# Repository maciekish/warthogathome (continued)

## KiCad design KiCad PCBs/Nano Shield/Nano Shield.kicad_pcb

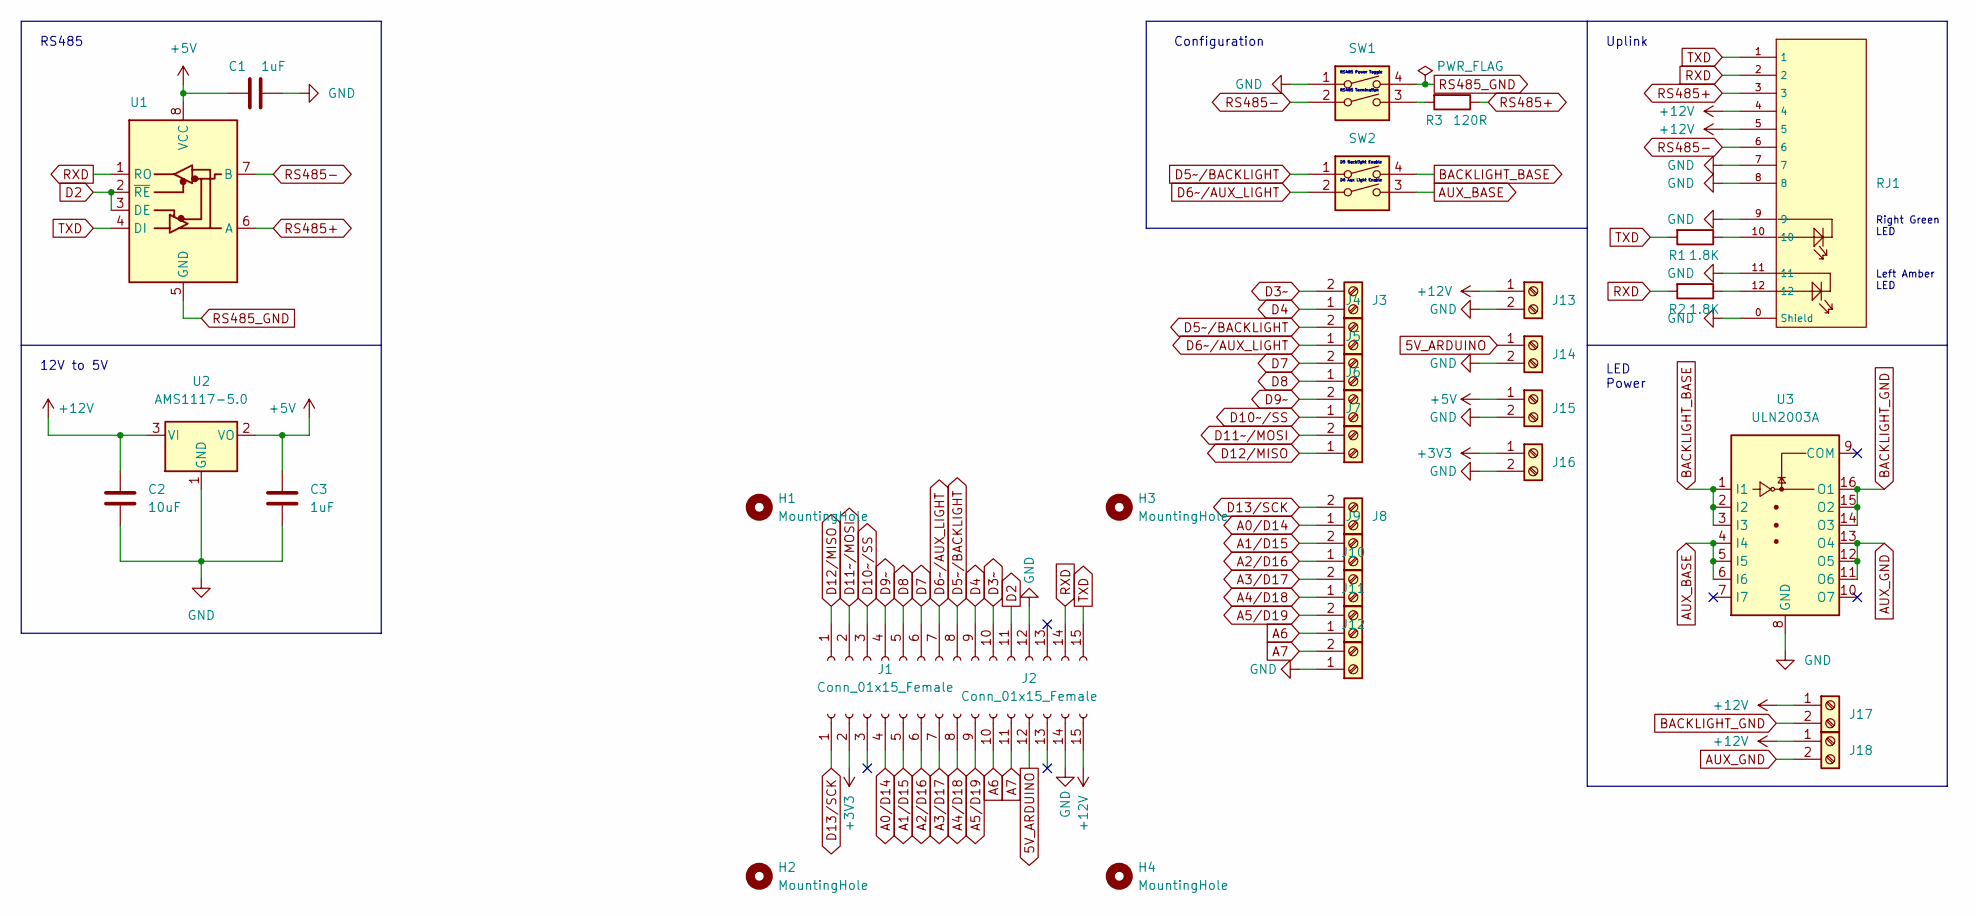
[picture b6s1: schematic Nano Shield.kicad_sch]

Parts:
C1, C3: 1uF; C0402; LCSC C52923
C2: 10uF; C0402; LCSC C15525
H1: MountingHole
H2, H3, H4: MountingHole; MountingHole_3.2mm_M3
J1, J2: Conn_01x15_Female; PinSocket_1x15_P2.54mm_Vertical
J3, J4, J5, J6, J7, J8, J9, J10, J11, J12, J13, J14, J15, J16, J17, J18: Screw_Terminal_01x02; CONN-TH_XY308-2.54-2P; LCSC C557685
R1, R2: 1.8K; R_0805_2012Metric; LCSC C17398
R3: 120R; R_0805_2012Metric; LCSC C17437
RJ1: RJ45-B-1*1; RJ45-TH_B-1-1; LCSC C138392
SW1, SW2: SW_DIP_x02; SW-SMD_DSHP02TSGER; LCSC C367376
U1: MAX487ESA+T; SOIC-8_L5.0-W4.0-P1.27-LS6.0-BL; LCSC C9953
U2: AMS1117-5.0; SOT-223-3_TabPin2; LCSC C6187
U3: ULN2003A; SOP-16_L10.0-W3.9-P1.27-LS6.0-BL; LCSC C7512

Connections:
5V_ARDUINO: J2.12, J14.1
+3V3: J2.2, J16.1
+5V: C1.1, C3.1, J15.1, U1.8 (VCC), U2.2 (VO)
+12V: C2.1, J2.15, J13.1, J17.1, J18.1, RJ1.4, RJ1.5, U2.3 (VI)
A0/D14: J2.4, J8.1
A1/D15: J2.5, J9.2
A2/D16: J2.6, J9.1
A3/D17: J2.7, J10.2
A4/D18: J2.8, J10.1
A5/D19: J2.9, J11.2
A6: J2.10, J11.1
A7: J2.11, J12.2
AUX_BASE: SW2.3, U3.4 (I4), U3.5 (I5), U3.6 (I6)
AUX_GND: J18.2, U3.11 (O6), U3.12 (O5), U3.13 (O4)
BACKLIGHT_BASE: SW2.4, U3.1 (I1), U3.2 (I2), U3.3 (I3)
BACKLIGHT_GND: J17.2, U3.14 (O3), U3.15 (O2), U3.16 (O1)
D2: J1.11, U1.2 (~RE), U1.3 (DE)
D3~: J1.10, J3.2
D4: J1.9, J3.1
D5~/BACKLIGHT: J1.8, J4.2, SW2.1
D6~/AUX_LIGHT: J1.7, J4.1, SW2.2
D7: J1.6, J5.2
D8: J1.5, J5.1
D9~: J1.4, J6.2
D10~/SS: J1.3, J6.1
D11~/MOSI: J1.2, J7.2
D12/MISO: J1.1, J7.1
D13/SCK: J2.1, J8.2
GND: C1.2, C2.2, C3.2, J1.12, J2.14, J12.1, J13.2, J14.2, J15.2, J16.2, RJ1.0 (Shield), RJ1.7, RJ1.8, RJ1.9, RJ1.11, SW1.1, U2.1 (GND), U3.8 (GND)
unnamed: R1.1, RJ1.10
unnamed: R2.1, RJ1.12
unnamed: R3.2, SW1.3
RS485+: R3.1, RJ1.3, U1.6 (A)
RS485-: RJ1.6, SW1.2, U1.7 (B)
RS485_GND: SW1.4, U1.5 (GND)
RXD: J1.14, R2.2, RJ1.2, U1.1 (RO)
TXD: J1.15, R1.2, RJ1.1, U1.4 (DI)

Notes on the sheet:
D5 Backlight Enable
LED Power
Right Green LED
RS485 Power Toggle
Uplink
12V to 5V
D6 Aux Light Enable
Left Amber LED
RS485 Termination
Configuration
RS485

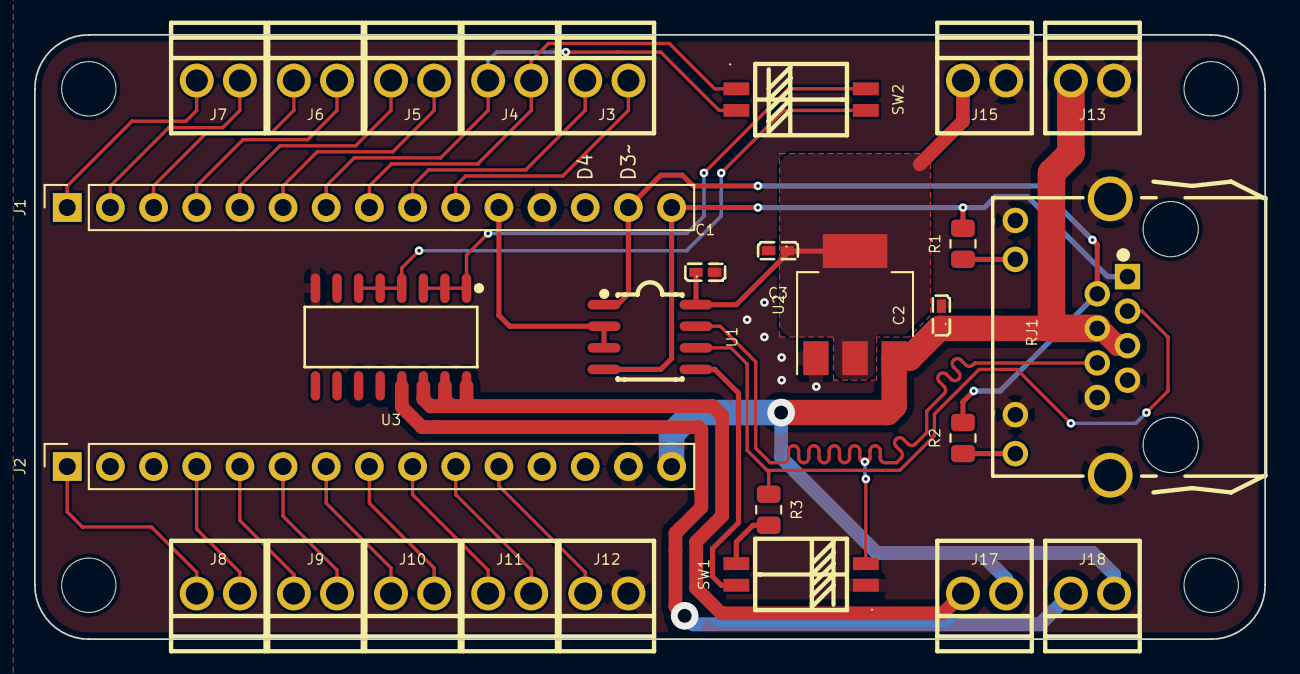
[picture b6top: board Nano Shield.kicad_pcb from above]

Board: 2 copper layers, 72.4 x 35.6 mm, 32 parts (0 on the bottom side), 35 nets.

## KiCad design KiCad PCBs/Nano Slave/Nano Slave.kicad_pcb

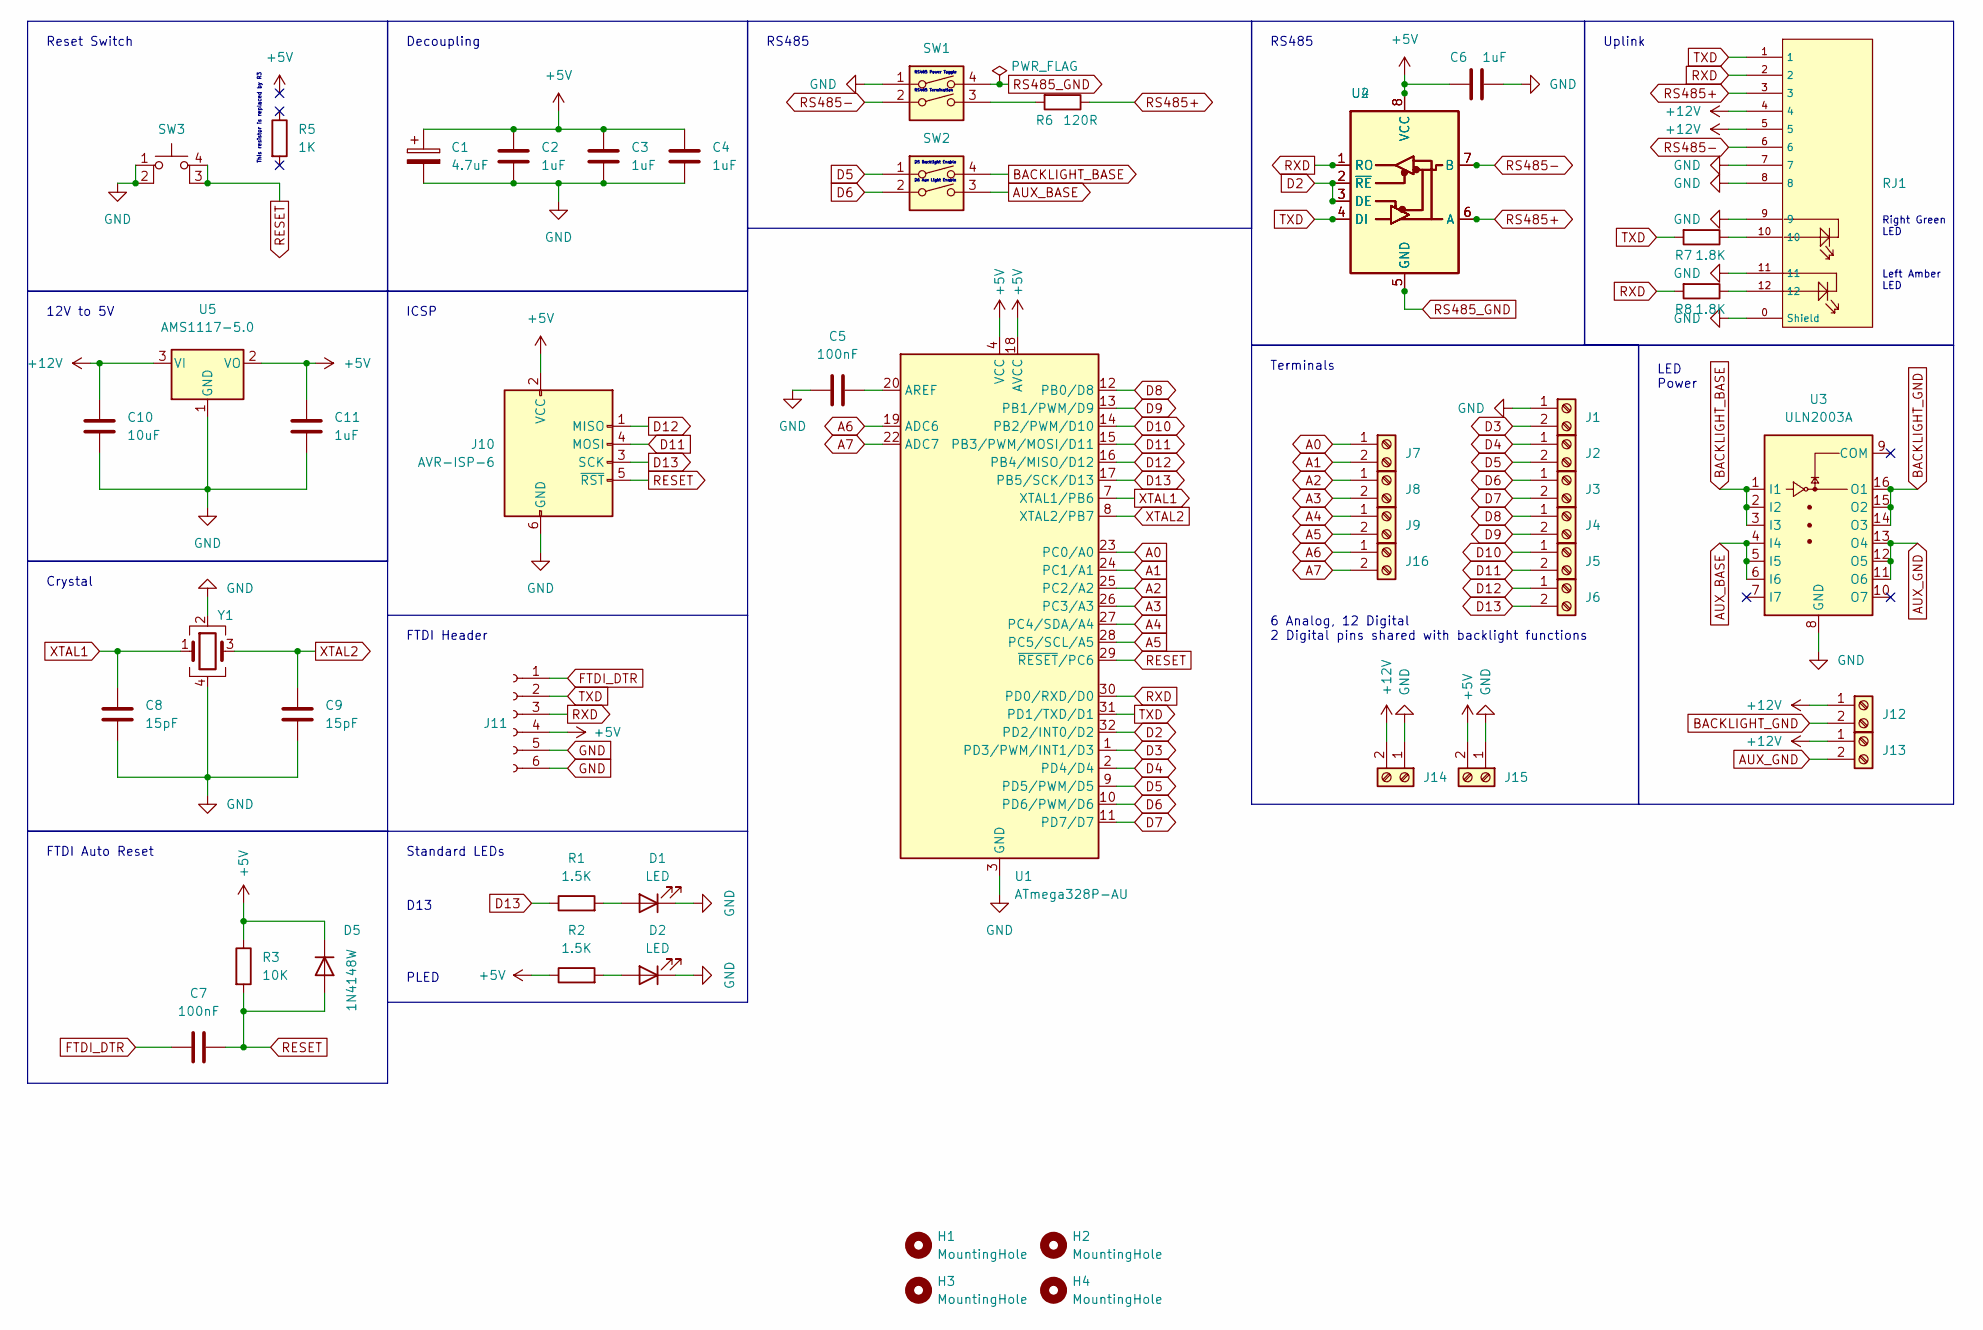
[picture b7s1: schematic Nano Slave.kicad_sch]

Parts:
C1: 4.7uF; C0805; LCSC C1779
C2, C3, C4, C6, C11: 1uF; C0402; LCSC C52923
C5, C7: 100nF; C0402; LCSC C1525
C8, C9: 15pF; C0402; LCSC C1548
C10: 10uF; C0402; LCSC C15525
D1, D2: LED; LED_0603_1608Metric; LCSC C72041
D5: 1N4148W; D_SOD-123; LCSC C81598
H1, H2, H3, H4: MountingHole; MountingHole_3.2mm_M3
J1, J2, J3, J4, J5, J6, J7, J8, J9, J12, J13, J14, J15, J16: Screw_Terminal_01x02; CONN-TH_WJ126V-5.0-2P; LCSC C8404
J10: AVR-ISP-6; PinHeader_2x03_P2.54mm_Vertical; LCSC C492420
J11: Conn_01x06_Female; PinSocket_1x06_P2.54mm_Vertical; LCSC C40877
R1, R2: 1.5K; R_0805_2012Metric; LCSC C4310
R3: 10K; R_0805_2012Metric; LCSC C17414
R5: 1K; R_0805_2012Metric; LCSC C17513
R6: 120R; R_0805_2012Metric; LCSC C17437
R7, R8: 1.8K; R_0805_2012Metric; LCSC C17398
RJ1: RJ45-B-1*1; RJ45-TH_B-1-1; LCSC C138392
SW1, SW2: SW_DIP_x02; SW-SMD_DSHP02TSGER; LCSC C367376
SW3: SW_MEC_5E; SW-SMD_4P-L5.1-W5.1-P3.70-LS6.5-TL-2; LCSC C318884
U1: ATmega328P-AU; TQFP-32_7x7mm_P0.8mm; LCSC C14877
U2: MAX487ESA+T; SOIC-8_L5.0-W4.0-P1.27-LS6.0-BL; LCSC C9953
U3: ULN2003A; SOP-16_L10.0-W3.9-P1.27-LS6.0-BL; LCSC C7512
U4: MAX487CPA+; DIP-8_W7.62mm
U5: AMS1117-5.0; SOT-223-3_TabPin2; LCSC C6187
Y1: Crystal_GND24; Crystal_SMD_3225-4Pin_3.2x2.5mm; LCSC C13738

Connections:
+5V: C1.1, C2.1, C3.1, C4.1, C6.1, C11.1, D5.1 (K), J10.2 (VCC), J11.4, J15.2, R2.1, R3.1, U1.4 (VCC), U1.6 (VCC), U1.18 (AVCC), U2.8 (VCC), U4.8 (VCC), U5.2 (VO)
+12V: C10.1, J12.1, J13.1, J14.2, RJ1.4, RJ1.5, U5.3 (VI)
A0: J7.1, U1.23 (PC0/A0)
A1: J7.2, U1.24 (PC1/A1)
A2: J8.1, U1.25 (PC2/A2)
A3: J8.2, U1.26 (PC3/A3)
A4: J9.1, U1.27 (PC4/SDA/A4)
A5: J9.2, U1.28 (PC5/SCL/A5)
A6: J16.1, U1.19 (ADC6)
A7: J16.2, U1.22 (ADC7)
AUX_BASE: SW2.3, U3.4 (I4), U3.5 (I5), U3.6 (I6)
AUX_GND: J13.2, U3.11 (O6), U3.12 (O5), U3.13 (O4)
BACKLIGHT_BASE: SW2.4, U3.1 (I1), U3.2 (I2), U3.3 (I3)
BACKLIGHT_GND: J12.2, U3.14 (O3), U3.15 (O2), U3.16 (O1)
D2: U1.32 (PD2/INT0/D2), U2.2 (~RE), U2.3 (DE), U4.2 (~RE), U4.3 (DE)
D3: J1.2, U1.1 (PD3/PWM/INT1/D3)
D4: J2.1, U1.2 (PD4/D4)
D5: J2.2, SW2.1, U1.9 (PD5/PWM/D5)
D6: J3.1, SW2.2, U1.10 (PD6/PWM/D6)
D7: J3.2, U1.11 (PD7/D7)
D8: J4.1, U1.12 (PB0/D8)
D9: J4.2, U1.13 (PB1/PWM/D9)
D10: J5.1, U1.14 (PB2/PWM/D10)
D11: J5.2, J10.4 (MOSI), U1.15 (PB3/PWM/MOSI/D11)
D12: J6.1, J10.1 (MISO), U1.16 (PB4/MISO/D12)
D13: J6.2, J10.3 (SCK), R1.1, U1.17 (PB5/SCK/D13)
FTDI_DTR: C7.2, J11.1
GND: C1.2, C2.2, C3.2, C4.2, C5.1, C6.2, C8.1, C9.2, C10.2, C11.2, D1.1 (K), D2.1 (K), J1.1, J10.6 (GND), J11.5, J11.6, J14.1, J15.1, RJ1.0 (Shield), RJ1.7, RJ1.8, RJ1.9, RJ1.11, SW1.1, SW3.1, SW3.2, U1.3 (GND), U1.5 (GND), U1.21 (GND), U3.8 (GND), U5.1 (GND), Y1.2, Y1.4
unnamed: C5.2, U1.20 (AREF)
unnamed: D1.2 (A), R1.2
unnamed: D2.2 (A), R2.2
unnamed: R6.2, SW1.3
unnamed: R7.1, RJ1.10
unnamed: R8.1, RJ1.12
RESET: C7.1, D5.2 (A), J10.5 (~RST), R3.2, SW3.3 (K), SW3.4 (A), U1.29 (~RESET/PC6)
RS485+: R6.1, RJ1.3, U2.6 (A), U4.6 (A)
RS485-: RJ1.6, SW1.2, U2.7 (B), U4.7 (B)
RS485_GND: SW1.4, U2.5 (GND), U4.5 (GND)
RXD: J11.3, R8.2, RJ1.2, U1.30 (PD0/RXD/D0), U2.1 (RO), U4.1 (RO)
TXD: J11.2, R7.2, RJ1.1, U1.31 (PD1/TXD/D1), U2.4 (DI), U4.4 (DI)
XTAL1: C8.2, U1.7 (XTAL1/PB6), Y1.1
XTAL2: C9.1, U1.8 (XTAL2/PB7), Y1.3

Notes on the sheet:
RS485
Decoupling
Left Amber LED
D13
12V to 5V
Uplink
D5 Backlight Enable
RS485 Power Toggle
6 Analog, 12 Digital 2 Digital pins shared with backlight functions
Terminals
RS485 Termination
PLED
FTDI Header
D6 Aux Light Enable
Standard LEDs
LED Power
Right Green LED
FTDI Auto Reset
Reset Switch
Crystal
ICSP
This resistor is replaced by R3

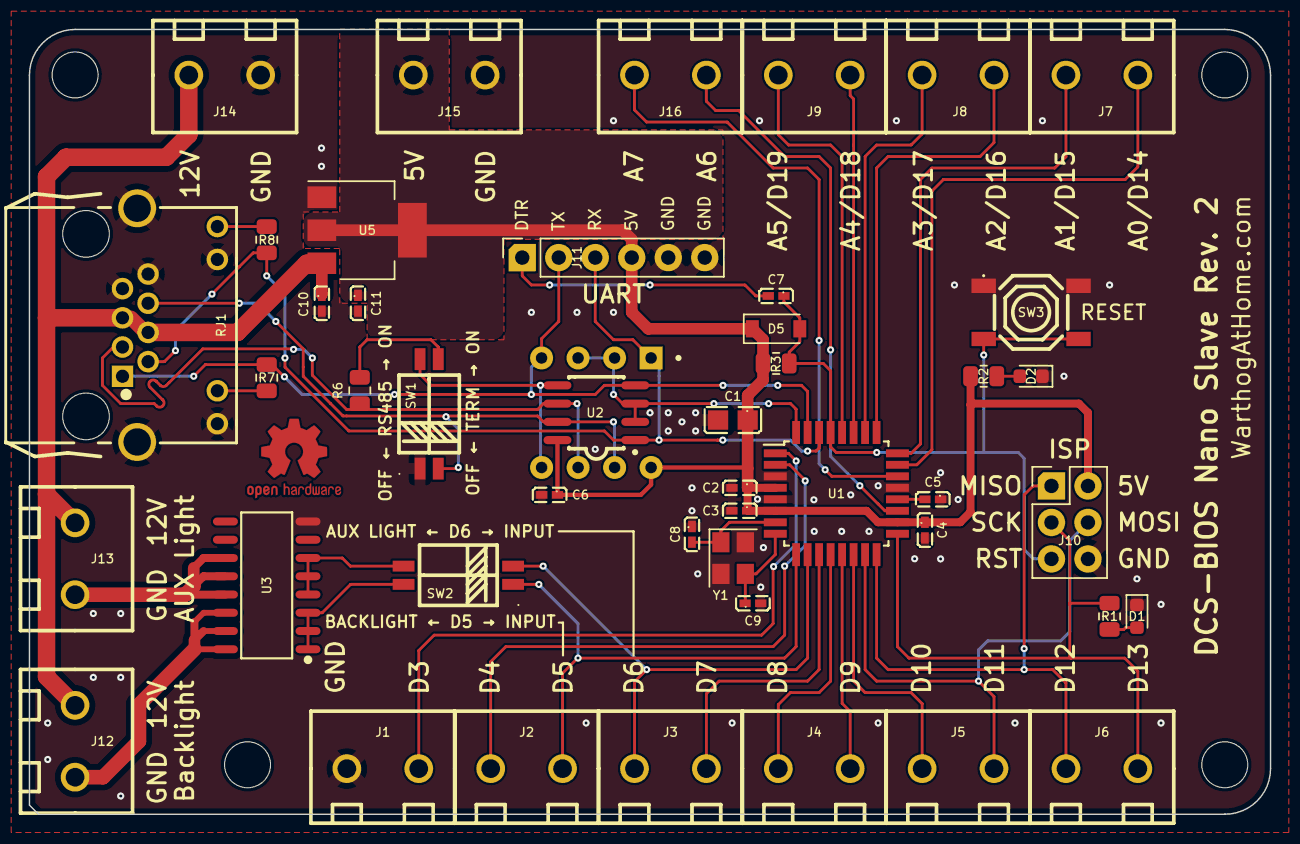
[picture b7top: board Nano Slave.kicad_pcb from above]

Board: 2 copper layers, 86.4 x 54.6 mm, 50 parts (0 on the bottom side), 42 nets.
